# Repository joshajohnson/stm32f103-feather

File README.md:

# STM32F103 Feather

## STM32F103 in an Adafruit Feather form factor.
- STM32F103 MCU
- USB type C connector
- SWD Header
- RGB LED
- Designed to work with my [RF Signal Generator](https://github.com/joshajohnson/rf-sig-gen)

### TODO

#### Hardware
- [ ] Optimise pin mapping for V0.2 (SPI1 CS incorrecly positioned, may be other issues)

#### Firmware
- [ ] Improved demo code
- [ ] PWM control drivers for RGB LED
- [ ] USB Bootloader
- [ ] Add to Arduino framework with STM32Duino
- [ ] Add Black Magic Probe support?

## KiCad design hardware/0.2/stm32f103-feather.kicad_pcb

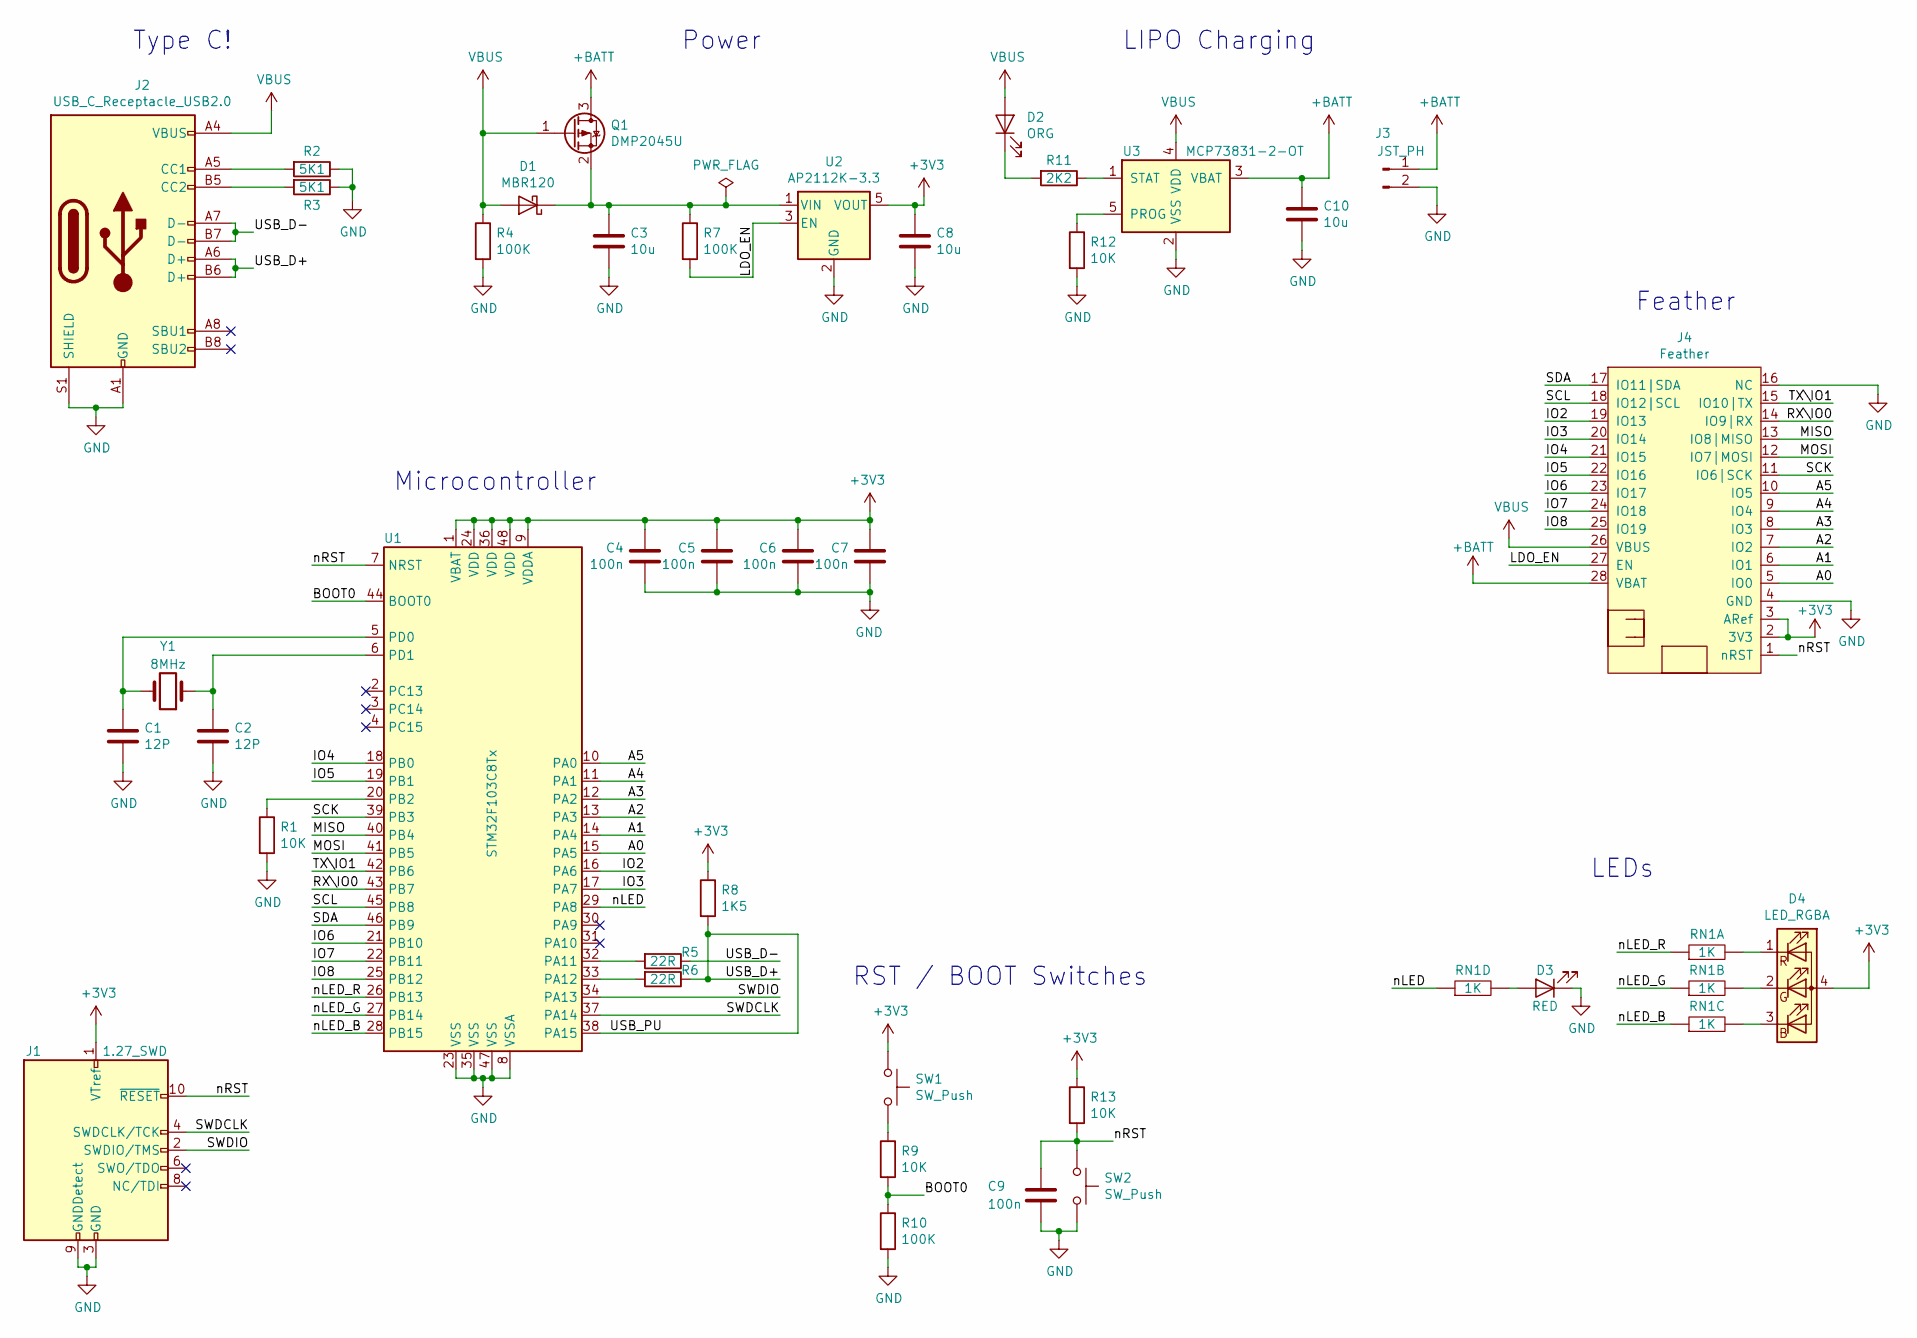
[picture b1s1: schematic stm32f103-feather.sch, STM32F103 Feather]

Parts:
C1, C2: 12P; C_0603_1608Metric
C3, C8, C10: 10u; C_0603_1608Metric
C4, C5, C6, C7, C9: 100n; C_0603_1608Metric
D1: MBR120; D_SOD-123FL
D2: ORG; LED_0603_1608Metric_Castellated
D3: RED; LED_0603_1608Metric_Castellated
D4: LED_RGBA; LED_0606_E6C0606RGBC3UDA
J1: 1.27_SWD; SAMTEC_FTSH-105-01-L-DV-R-TR
J2: USB_C_Receptacle_USB2.0; USB_C_Receptacle_GT-USB-7010
J3: JST_PH; JST_PH_S2B-PH-SM4-TB_1x02-1MP_P2.00mm_Horizontal
J4: Feather; featherwing-typeC
Q1: DMP2045U; SOT-23
R1, R9, R12, R13: 10K; R_0603_1608Metric
R2, R3: 5K1; R_0603_1608Metric
R4, R7, R10: 100K; R_0603_1608Metric
R5, R6: 22R; R_0603_1608Metric
R8: 1K5; R_0603_1608Metric
R11: 2K2; R_0603_1608Metric
RN1: 1K; R_Array_Convex_4x0402
SW1, SW2: SW_Push; BT_PTS815
U1: STM32F103C8Tx; LQFP-48_7x7mm_P0.5mm
U2: AP2112K-3.3; SOT-23-5
U3: MCP73831-2-OT; SOT-23-5
Y1: 8MHz; Crystal_SMD_5032-2Pin_5.0x3.2mm

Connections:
+3V3: C4.1, C5.1, C6.1, C7.1, C8.1, D4.4 (A), J1.1 (VTref), J4.2 (3V3), J4.3 (ARef), R8.1, R13.1, SW1.1, U1.1 (VBAT), U1.9 (VDDA), U1.24 (VDD), U1.36 (VDD), U1.48 (VDD), U2.5 (VOUT)
+BATT: C10.1, J3.1, J4.28 (VBAT), Q1.3 (D), U3.3 (VBAT)
/A0: J4.5 (IO0), U1.15 (PA5)
/A1: J4.6 (IO1), U1.14 (PA4)
/A2: J4.7 (IO2), U1.13 (PA3)
/A3: J4.8 (IO3), U1.12 (PA2)
/A4: J4.9 (IO4), U1.11 (PA1)
/A5: J4.10 (IO5), U1.10 (PA0)
/BOOT0: R9.2, R10.1, U1.44 (BOOT0)
/IO2: J4.19 (IO13), U1.16 (PA6)
/IO3: J4.20 (IO14), U1.17 (PA7)
/IO4: J4.21 (IO15), U1.18 (PB0)
/IO5: J4.22 (IO16), U1.19 (PB1)
/IO6: J4.23 (IO17), U1.21 (PB10)
/IO7: J4.24 (IO18), U1.22 (PB11)
/IO8: J4.25 (IO19), U1.25 (PB12)
/LDO_EN: J4.27 (EN), R7.2, U2.3 (EN)
/MISO: J4.13 (IO8|MISO), U1.40 (PB4)
/MOSI: J4.12 (IO7|MOSI), U1.41 (PB5)
/RX\IO0: J4.14 (IO9|RX), U1.43 (PB7)
/SCK: J4.11 (IO6|SCK), U1.39 (PB3)
/SCL: J4.18 (IO12|SCL), U1.45 (PB8)
/SDA: J4.17 (IO11|SDA), U1.46 (PB9)
/SWDCLK: J1.4 (SWDCLK/TCK), U1.37 (PA14)
/SWDIO: J1.2 (SWDIO/TMS), U1.34 (PA13)
/TX\IO1: J4.15 (IO10|TX), U1.42 (PB6)
/USB_D+: J2.A6 (D+), J2.B6 (D+), R6.1, R8.2, U1.38 (PA15)
/USB_D-: J2.A7 (D-), J2.B7 (D-), R5.1
/nLED: RN1.1, U1.29 (PA8)
/nLED_B: RN1.2, U1.28 (PB15)
/nLED_G: RN1.3, U1.27 (PB14)
/nLED_R: RN1.4, U1.26 (PB13)
/nRST: C9.1, J1.10 (~RESET~), J4.1 (nRST), R13.2, SW2.1, U1.7 (NRST)
GND: C1.2, C2.2, C3.2, C4.2, C5.2, C6.2, C7.2, C8.2, C9.2, C10.2, D3.1 (K), J1.3 (GND), J1.5 (GND), J1.9 (GNDDetect), J2.A1 (GND), J2.A12 (GND), J2.B1 (GND), J2.B12 (GND), J2.S1 (SHIELD), J3.2, J4.4 (GND), J4.16 (NC), R1.2, R2.1, R3.1, R4.2, R10.2, R12.2, SW2.2, U1.8 (VSSA), U1.23 (VSS), U1.35 (VSS), U1.47 (VSS), U2.2 (GND), U3.2 (VSS)
unnamed: C1.1, U1.5 (PD0), Y1.2
unnamed: C2.1, U1.6 (PD1), Y1.1
unnamed: C3.1, D1.1 (K), Q1.2 (S), R7.1, U2.1 (VIN)
unnamed: D2.1 (K), R11.2
unnamed: D3.2 (A), RN1.8
unnamed: D4.1 (RK), RN1.5
unnamed: D4.2 (GK), RN1.6
unnamed: D4.3 (BK), RN1.7
unnamed: J2.A5 (CC1), R2.2
unnamed: J2.B5 (CC2), R3.2
unnamed: R1.1, U1.20 (PB2)
unnamed: R5.2, U1.32 (PA11)
unnamed: R6.2, U1.33 (PA12)
unnamed: R9.1, SW1.2
unnamed: R11.1, U3.1 (STAT)
unnamed: R12.1, U3.5 (PROG)
VBUS: D1.2 (A), D2.2 (A), J2.A4 (VBUS), J2.A9 (VBUS), J2.B4 (VBUS), J2.B9 (VBUS), J4.26 (VBUS), Q1.1 (G), R4.1, U3.4 (VDD)

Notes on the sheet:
RST / BOOT Switches
Feather
Microcontroller
Type C!
Power
LIPO Charging
LEDs

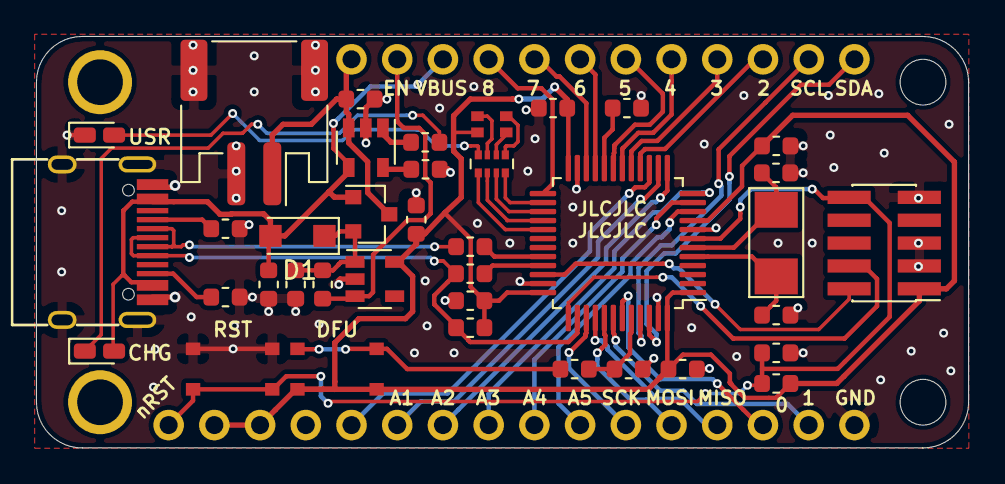
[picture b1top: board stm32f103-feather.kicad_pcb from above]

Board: 2 copper layers, 51.8 x 22.9 mm, 39 parts (0 on the bottom side), 51 nets.

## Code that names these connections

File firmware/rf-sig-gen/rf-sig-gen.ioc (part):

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Mcu.Name=STM32F103C(8-B)Tx
Mcu.Package=LQFP48
Mcu.UserName=STM32F103C8Tx
PA0-WKUP.GPIOParameters=GPIO_Label
PA0-WKUP.GPIO_Label=RF_PWR
PA0-WKUP.Signal=ADCx_IN0
PA1.GPIOParameters=GPIO_Label
PA1.GPIO_Label=MAX_LE
PA1.Signal=GPIO_Output
PA11.Mode=Device
PA11.Signal=USB_DM
PA12.Mode=Device
PA12.Signal=USB_DP
PA13.GPIOParameters=GPIO_Label
PA13.GPIO_Label=SWDIO
PA13.Mode=Serial_Wire
PA13.Signal=SYS_JTMS-SWDIO
PA14.GPIOParameters=GPIO_Label
PA14.GPIO_Label=SWDCLK
PA14.Mode=Serial_Wire
PA14.Signal=SYS_JTCK-SWCLK
PA15.GPIOParameters=GPIO_Label
PA15.GPIO_Label=USB_PU
PA15.Signal=GPIO_Input
PA2.GPIOParameters=GPIO_Label
PA2.GPIO_Label=MAX_RFOUT_EN
PA2.Signal=GPIO_Output
PA3.GPIOParameters=GPIO_Label
PA3.GPIO_Label=MAX_LD
PA3.Signal=GPIO_Input
PA5.GPIOParameters=GPIO_Label
PA5.GPIO_Label=nLED_OE
PA5.Signal=GPIO_Output
PA6.GPIOParameters=GPIO_Label
PA6.GPIO_Label=ATTEN_LE
PA6.Signal=GPIO_Input
PA7.GPIOParameters=GPIO_Label
PA7.GPIO_Label=ATTEN_SDI
PA7.Signal=GPIO_Output
PA8.GPIOParameters=GPIO_Label
PA8.GPIO_Label=nLED_USR
PA8.Signal=GPIO_Output
PB0.GPIOParameters=GPIO_Label
PB0.GPIO_Label=ATTEN_CLK
PB0.Signal=GPIO_Output
PB10.GPIOParameters=GPIO_Label
PB10.GPIO_Label=LED_SDI
PB10.Signal=GPIO_Output
PB11.GPIOParameters=GPIO_Label
PB11.GPIO_Label=LED_CLK
PB11.Signal=GPIO_Output
PB12.GPIOParameters=GPIO_Label
PB12.GPIO_Label=LED_LE
PB12.Signal=GPIO_Output
PB13.GPIOParameters=GPIO_Label
PB13.GPIO_Label=nLED_RED
PB13.Mode=Output Compare1 CH1N
PB13.Signal=TIM1_CH1N
PB14.GPIOParameters=GPIO_Label
PB14.GPIO_Label=nLED_GRN
PB14.Mode=Output Compare2 CH2N
PB14.Signal=TIM1_CH2N
PB15.GPIOParameters=GPIO_Label
PB15.GPIO_Label=nLED_BLU
PB15.Mode=Output Compare3 CH3N
PB15.Signal=TIM1_CH3N
PB3.GPIOParameters=GPIO_Label
PB3.GPIO_Label=MAX_CE
PB3.Signal=GPIO_Output
PB4.GPIOParameters=GPIO_Label
PB4.GPIO_Label=MAX_DAT
PB4.Signal=GPIO_Output
PB5.GPIOParameters=GPIO_Label
PB5.GPIO_Label=MAX_CLK
PB5.Signal=GPIO_Output
PB6.GPIOParameters=GPIO_Label
PB6.GPIO_Label=LED
PB6.Signal=GPIO_Output
PB7.GPIOParameters=GPIO_Label
PB7.GPIO_Label=MAX_MUX
PB7.Signal=GPIO_Input
PB8.GPIOParameters=GPIO_Label
PB8.GPIO_Label=ATTEN_SDO
PB8.Signal=GPIO_Output
PB9.GPIOParameters=GPIO_Label
PB9.GPIO_Label=PA_PWDN
PB9.Signal=GPIO_Output
PD0-OSC_IN.Mode=HSE-External-Oscillator
PD0-OSC_IN.Signal=RCC_OSC_IN
PD1-OSC_OUT.Mode=HSE-External-Oscillator
PD1-OSC_OUT.Signal=RCC_OSC_OUT
RCC.SYSCLKFreq_VALUE=48000000
RCC.SYSCLKSource=RCC_SYSCLKSOURCE_PLLCLK
board=custom

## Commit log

2019-12-17 fixing submodule issues
2019-12-17 change osc footprint
2019-12-18 generated gerbers for V0.1
2019-12-31 got to blinky
2020-04-12 add gitignore
2020-04-12 board changes
2020-04-12 blinky working v2
2020-04-12 update gitignore
2020-04-12 schematic things
2020-04-12 uart working
2020-04-13 bitbang spi appears to work
2020-04-13 blinky update
2020-04-13 hardware
2020-04-19 rf working, leds not
2020-04-21 getting closer
2020-04-22 minimum viable sig gen
2020-04-27 move siggen firmware
2020-05-10 update documentation
2020-05-10 add license
2020-05-24 remove dupe
